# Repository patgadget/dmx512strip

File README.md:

# dmx512strip
DMX 512 full universe to strip of led ck/data<br>
-[Wiki access](https://github.com/patgadget/dmx512strip/wiki)<br>

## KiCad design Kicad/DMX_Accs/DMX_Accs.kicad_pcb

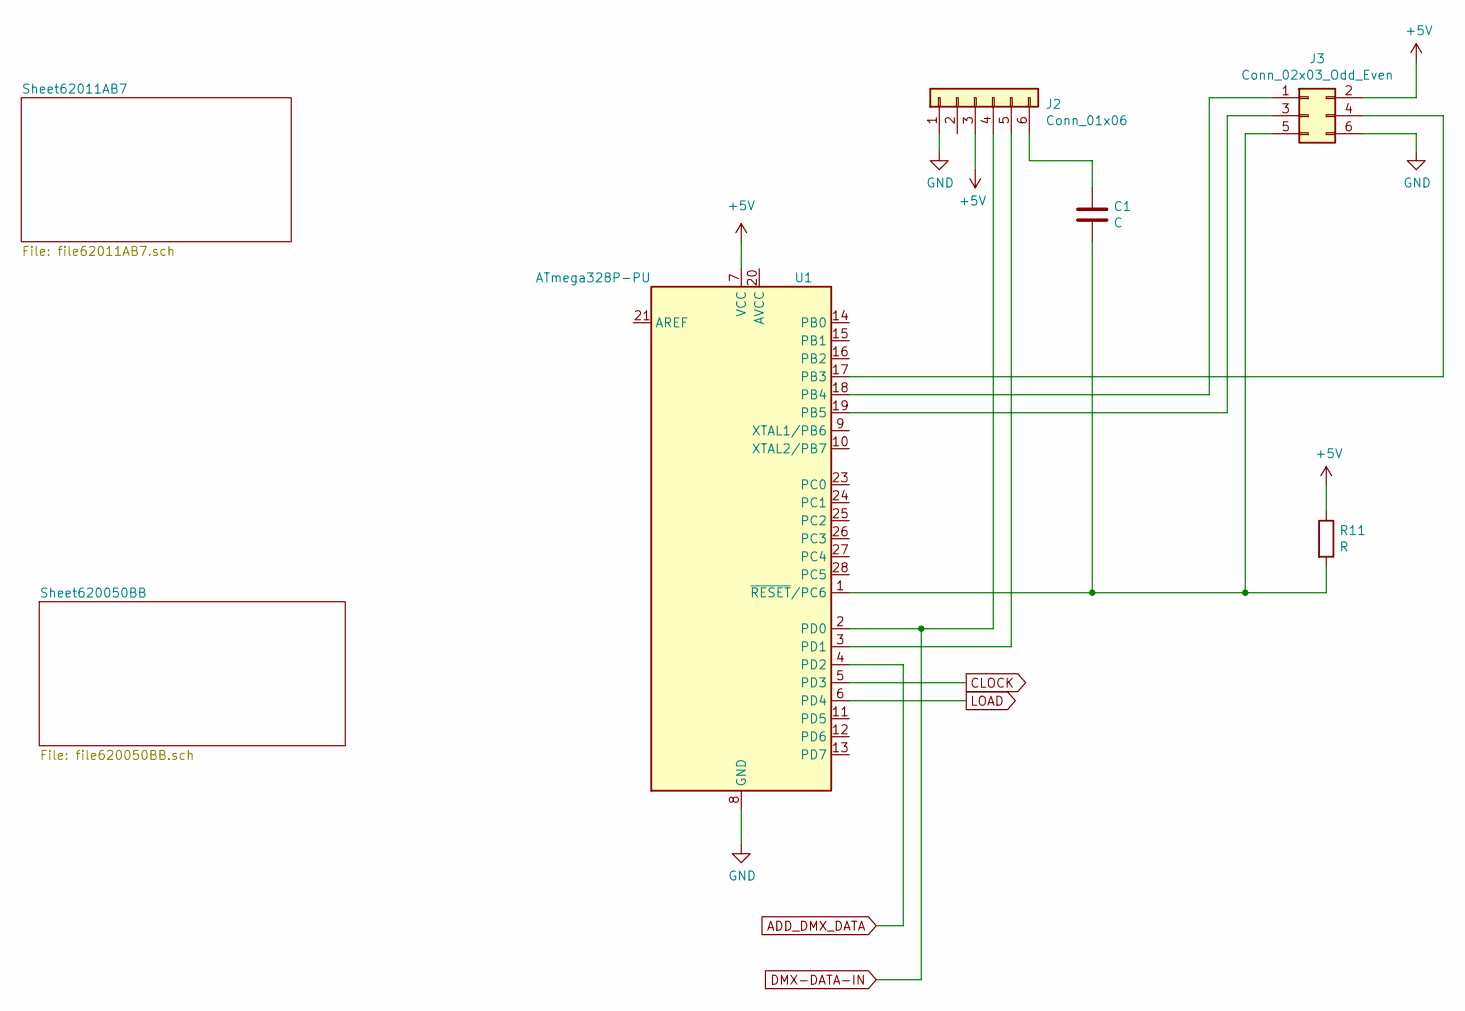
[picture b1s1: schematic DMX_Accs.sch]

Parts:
C1: C; C_Disc_D3.8mm_W2.6mm_P2.50mm
J2: Conn_01x06; PinHeader_1x06_P2.54mm_Vertical
J3: Conn_02x03_Odd_Even; PinHeader_2x03_P2.54mm_Vertical
R11: R; R_Axial_DIN0204_L3.6mm_D1.6mm_P7.62mm_Horizontal
U1: ATmega328P-PU; DIP-28_W7.62mm

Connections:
+5V: J2.3, J3.2, R11.1, U1.7 (VCC); also elsewhere on the board
ADD_DMX_DATA: U1.4 (PD2); also elsewhere on the board
CLOCK: U1.5 (PD3); also elsewhere on the board
DMX-DATA-IN: J2.4, U1.2 (PD0); also elsewhere on the board
GND: J2.1, J3.6, U1.8 (GND), U1.22 (GND); also elsewhere on the board
LOAD: U1.6 (PD4); also elsewhere on the board
unnamed: C1.1, J2.6
unnamed: C1.2, J3.5, R11.2, U1.1 (~RESET~/PC6)
unnamed: J2.5, U1.3 (PD1)
unnamed: J3.1, U1.18 (PB4)
unnamed: J3.3, U1.19 (PB5)
unnamed: J3.4, U1.17 (PB3)

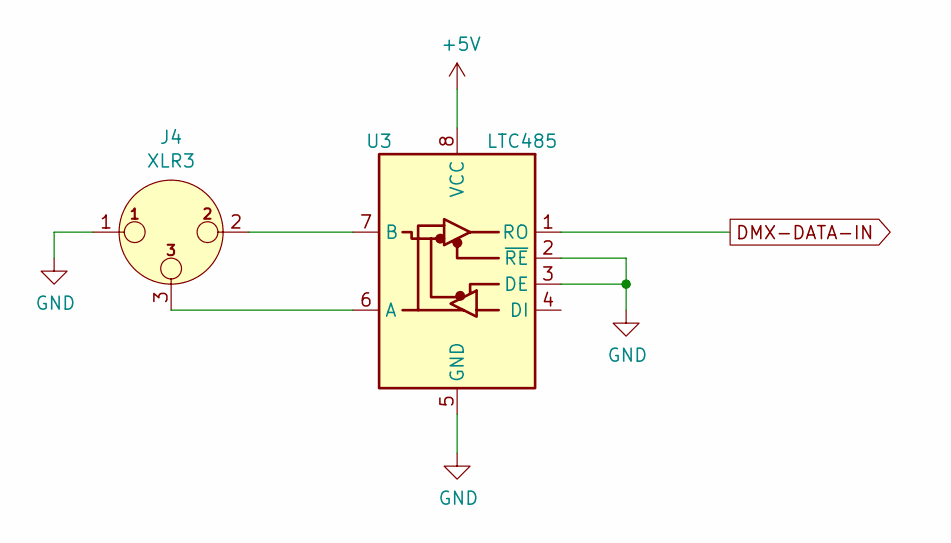
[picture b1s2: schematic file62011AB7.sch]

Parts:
J4: XLR3; PinHeader_1x03_P2.54mm_Vertical
U3: LTC485; DIP-8_W7.62mm

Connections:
+5V: U3.8 (VCC); also elsewhere on the board
DMX-DATA-IN: U3.1 (RO); also elsewhere on the board
GND: J4.1, U3.2 (~RE), U3.3 (DE), U3.5 (GND); also elsewhere on the board
unnamed: J4.2, U3.7 (B)
unnamed: J4.3, U3.6 (A)

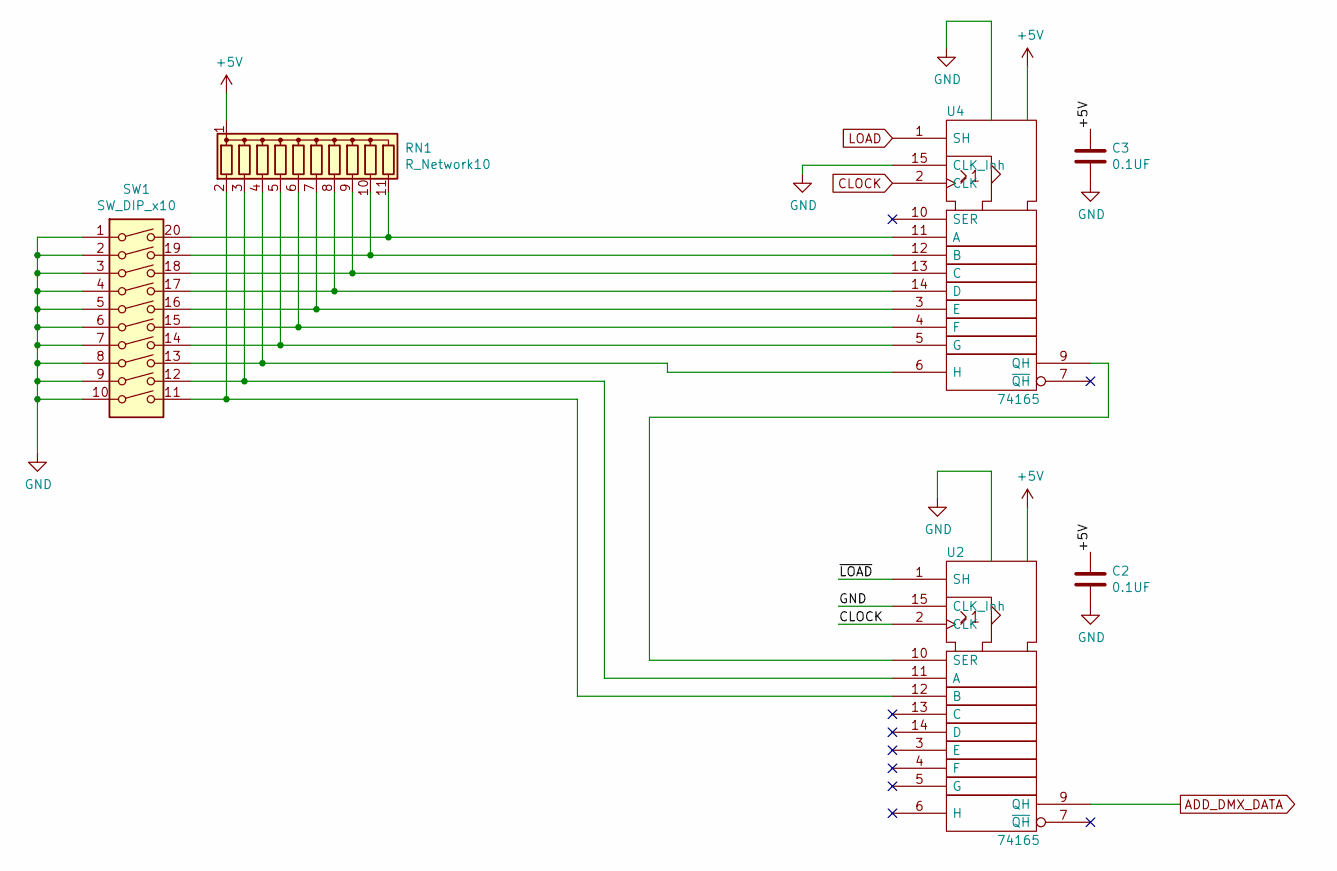
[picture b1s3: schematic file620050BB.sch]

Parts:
C2, C3: 0.1UF; C_Disc_D3.8mm_W2.6mm_P2.50mm
RN1: R_Network10; R_Array_SIP11
SW1: SW_DIP_x10; SW_DIP_SPSTx10_Piano_10.8x26.96mm_W7.62mm_P2.54mm
U2, U4: 74165; DIP-16_W7.62mm

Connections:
+5V: C2.1, C3.1, RN1.1 (common), U2.16 (VCC), U4.16 (VCC); also elsewhere on the board
ADD_DMX_DATA: U2.9 (QH); also elsewhere on the board
CLOCK: U2.2 (CLK), U4.2 (CLK); also elsewhere on the board
GND: C2.2, C3.2, SW1.1, SW1.2, SW1.3, SW1.4, SW1.5, SW1.6, SW1.7, SW1.8, SW1.9, SW1.10, U2.8 (GND), U2.15 (CLK_Inh), U4.8 (GND), U4.15 (CLK_Inh); also elsewhere on the board
LOAD: U4.1 (SH); also elsewhere on the board
unnamed: RN1.2 (R1), SW1.11, U2.12 (B)
unnamed: RN1.3 (R2), SW1.12, U2.11 (A)
unnamed: RN1.4 (R3), SW1.13, U4.6 (H)
unnamed: RN1.5 (R4), SW1.14, U4.5 (G)
unnamed: RN1.6 (R5), SW1.15, U4.4 (F)
unnamed: RN1.7 (R6), SW1.16, U4.3 (E)
unnamed: RN1.8 (R7), SW1.17, U4.14 (D)
unnamed: RN1.9 (R8), SW1.18, U4.13 (C)
unnamed: RN1.10 (R9), SW1.19, U4.12 (B)
unnamed: RN1.11 (R10), SW1.20, U4.11 (A)
unnamed: U2.10 (SER), U4.9 (QH)

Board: 2 copper layers, 13 parts (0 on the bottom side), 25 nets, no tracks yet.

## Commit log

2022-02-11 sdf
    asdf
2022-02-11 Delete Arduino_DMX_123.ino
    moved elsewhere
2022-02-11 Delete temp.txt
    temp file
